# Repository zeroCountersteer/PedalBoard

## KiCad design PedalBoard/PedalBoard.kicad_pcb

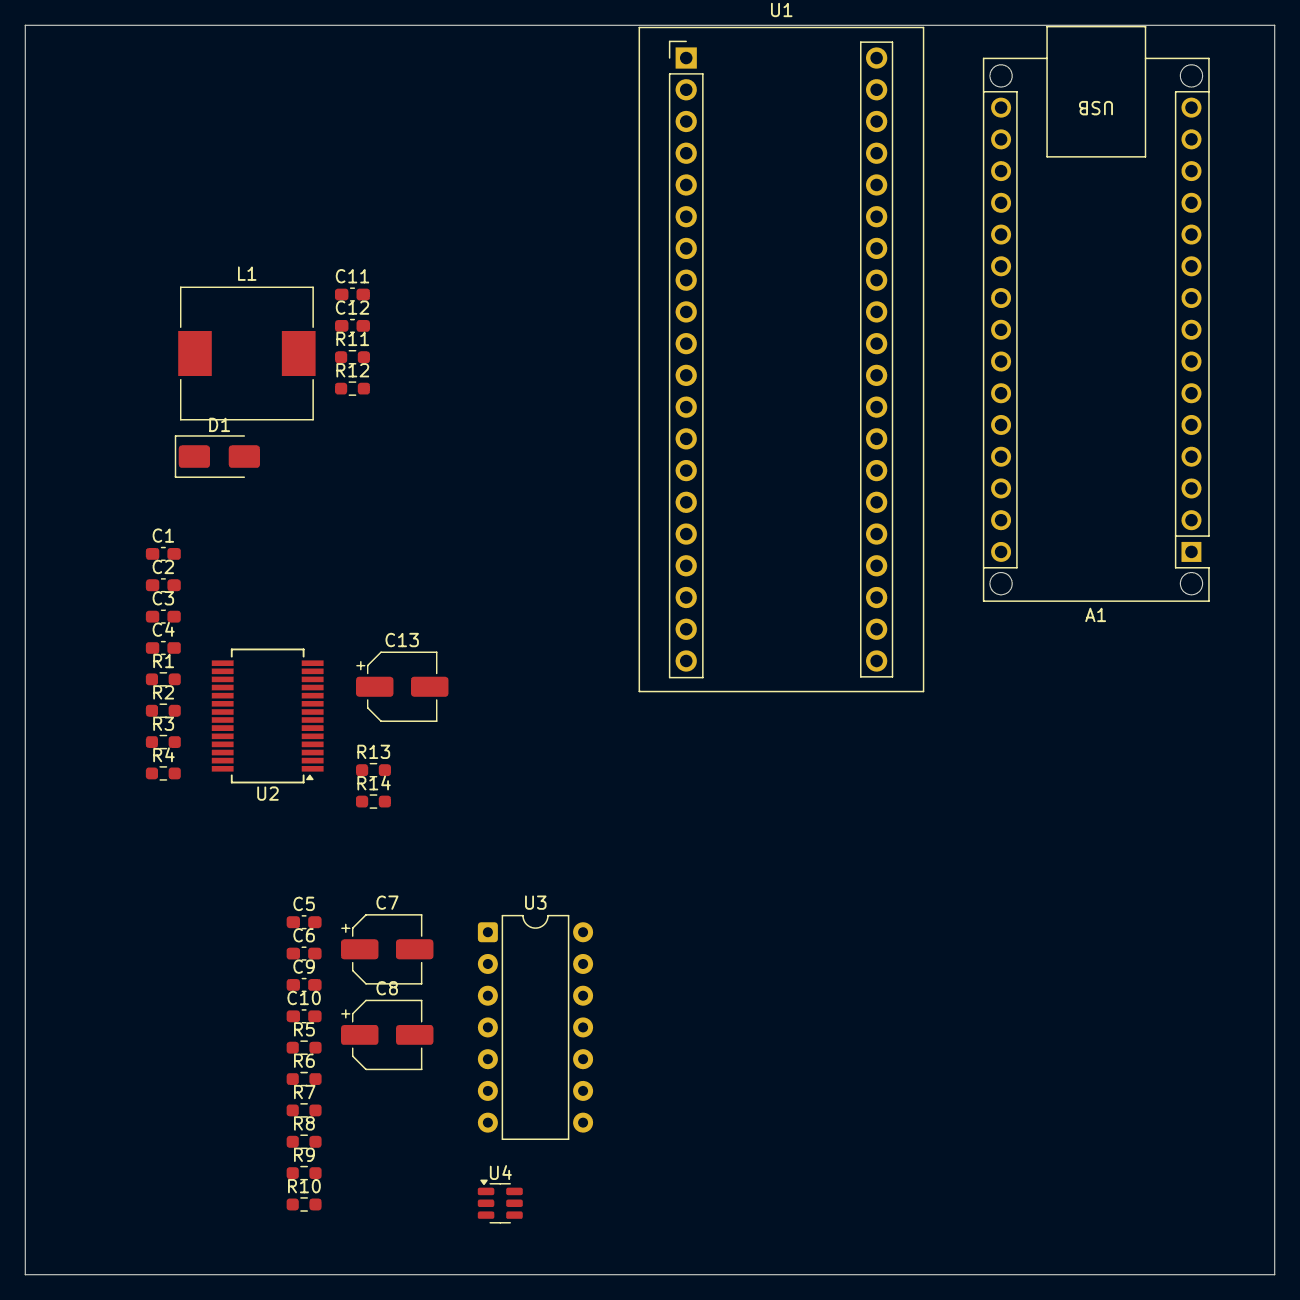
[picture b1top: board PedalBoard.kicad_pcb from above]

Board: 2 copper layers, 100.0 x 100.0 mm, 34 parts (0 on the bottom side), 27 nets, no tracks yet.

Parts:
A1: Arduino_Nano_ESP32; Arduino_Nano_WithMountingHoles
C1, C2, C5, C6, C9, C10, C11, C12: 1uF; C_0603_1608Metric_Pad1.08x0.95mm_HandSolder
C3, C4: 220pF; C_0603_1608Metric_Pad1.08x0.95mm_HandSolder
C7, C8: 220uF 6V3; CP_Elec_5x5.4
C13: 47uF 16V; CP_Elec_5x5.4
D1: SS34; D_SMA
L1: 22uH; L_10.4x10.4_H4.8
R1, R2, R3, R4: 5.6K; R_0603_1608Metric_Pad0.98x0.95mm_HandSolder
R5, R6: 100R; R_0603_1608Metric_Pad0.98x0.95mm_HandSolder
R7, R8, R9, R10: 47K; R_0603_1608Metric_Pad0.98x0.95mm_HandSolder
R11, R13, R14: 10K; R_0603_1608Metric_Pad0.98x0.95mm_HandSolder
R12: 200K; R_0603_1608Metric_Pad0.98x0.95mm_HandSolder
U1: YAAJ_BluePill_Part_Like; YAAJ_BluePill_2
U2: WM8731SEDS; SSOP-28_5.3x10.2mm_P0.65mm
U3: TL074; DIP-14_W7.62mm
U4: MT3608; SOT-23-6

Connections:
+3V3: U1.20 (3V3), U1.38 (3V3), U2.1 (DBVDD), U2.8 (HPVDD), U2.14 (AVDD), U2.27 (DCVDD)
+5V: C12.2, L1.1, U1.18 (5V), U4.4 (EN), U4.5 (IN)
+12V: C11.2, C13.1, D1.1 (K), R11.1, R13.1, U3.4 (V+)
/WM8731/ADCDAT: U1.12 (PB4), U2.6 (ADCDAT)
/WM8731/ADCLRC: U1.10 (PA15), U2.5 (DACLRC), U2.7 (ADCLRC)
/WM8731/BCLK: U1.11 (PB3), U2.3 (BCLK)
/WM8731/DACDAT: U1.13 (PB5), U2.4 (DACDAT)
/WM8731/SCLK: U1.14 (PB6), U2.24 (SCLK)
/WM8731/SDIN: U1.15 (PB7), U2.23 (SDIN)
/WM8731/XTI/MCLK: U1.5 (PA8), U2.25 (XTI/MCLK)
GND: C3.1, C4.1, C9.1, C10.1, C11.1, C12.1, C13.2, R1.2, R2.2, R7.2, R8.2, R9.2, R10.2, R12.2, R14.2, U1.19 (GND), U1.39 (GND), U1.40 (GND), U2.11 (HPGND), U2.15 (AGND), U2.21 (MODE), U2.22 (~CSB), U2.28 (DGND), U3.11 (V-), U4.2 (GND)
unnamed: A1.4 (GND), A1.29 (GND)
unnamed: C1.2, C4.2, R1.1, R4.1
unnamed: C2.2, C3.2, R2.1, R3.1
unnamed: C5.2, R5.1, R8.1
unnamed: C6.2, R6.1, R7.1
unnamed: D1.2 (A), L1.2, U4.1 (SW)
unnamed: C8.1, R9.1, U2.9 (LHPOUT)
unnamed: C1.1, U2.20 (LLINEIN)
unnamed: C5.1, U2.12 (LOUT)
unnamed: C7.1, R10.1, U2.10 (RHPOUT)
unnamed: C2.1, U2.19 (RLINEIN)
unnamed: C6.1, U2.13 (ROUT)
unnamed: C9.2, C10.2, U2.16 (VMID)
unnamed: R13.2, R14.1, U3.12 (+)
unnamed: U3.13 (-), U3.14
unnamed: R11.2, R12.1, U4.3 (FB)

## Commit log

2025-08-08 згшщав
